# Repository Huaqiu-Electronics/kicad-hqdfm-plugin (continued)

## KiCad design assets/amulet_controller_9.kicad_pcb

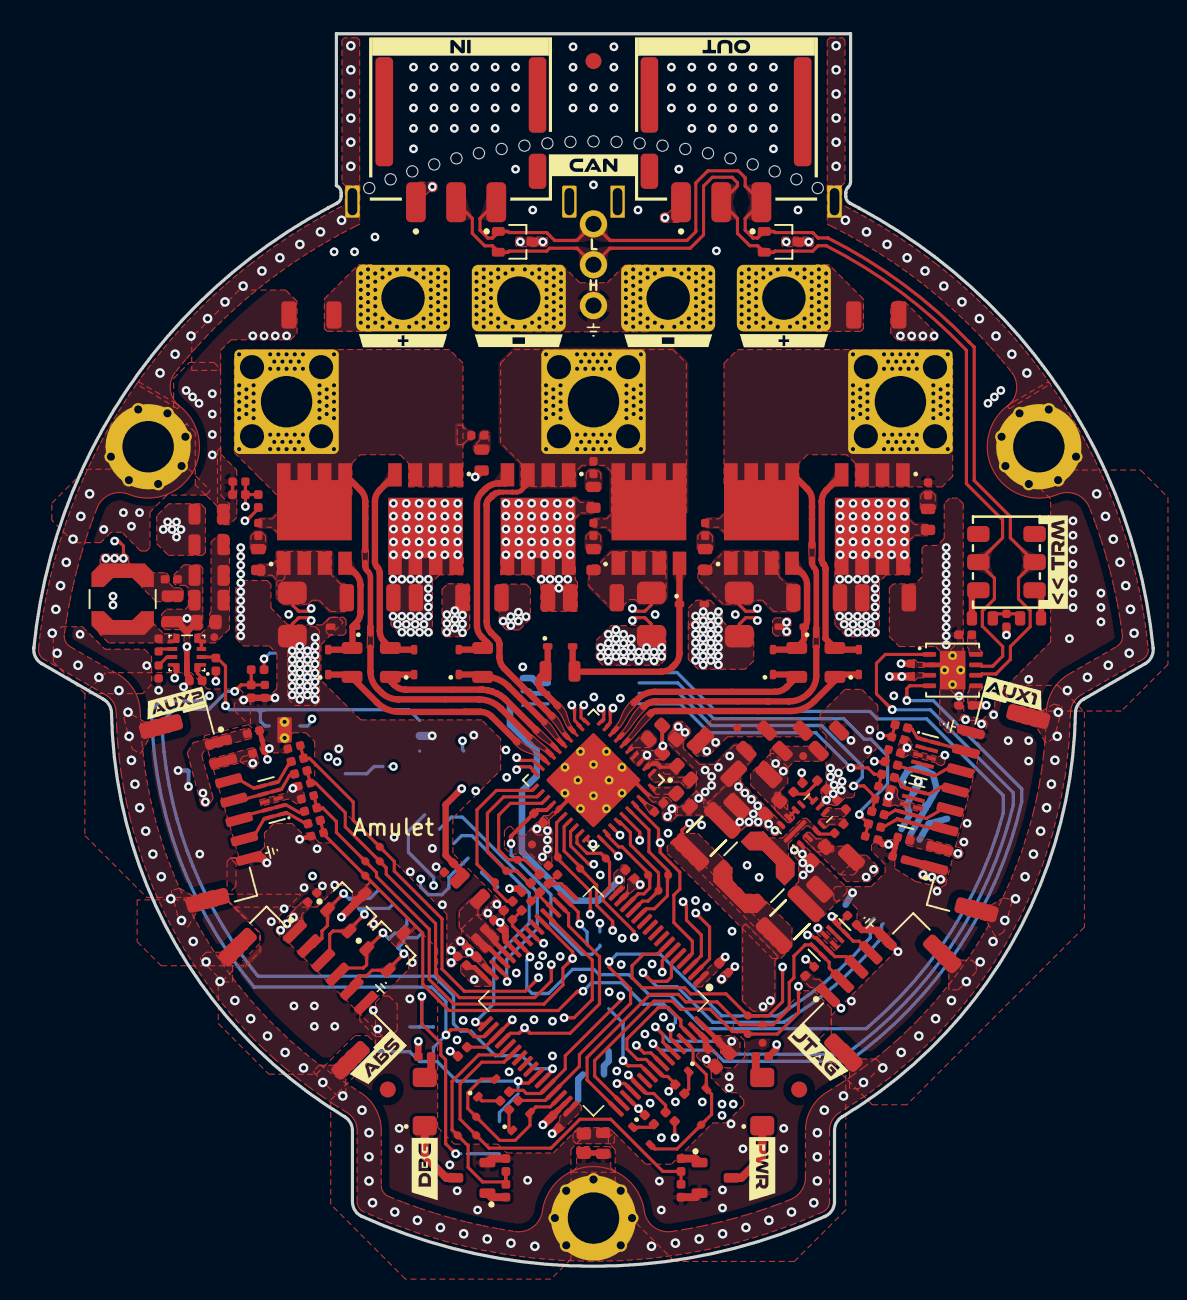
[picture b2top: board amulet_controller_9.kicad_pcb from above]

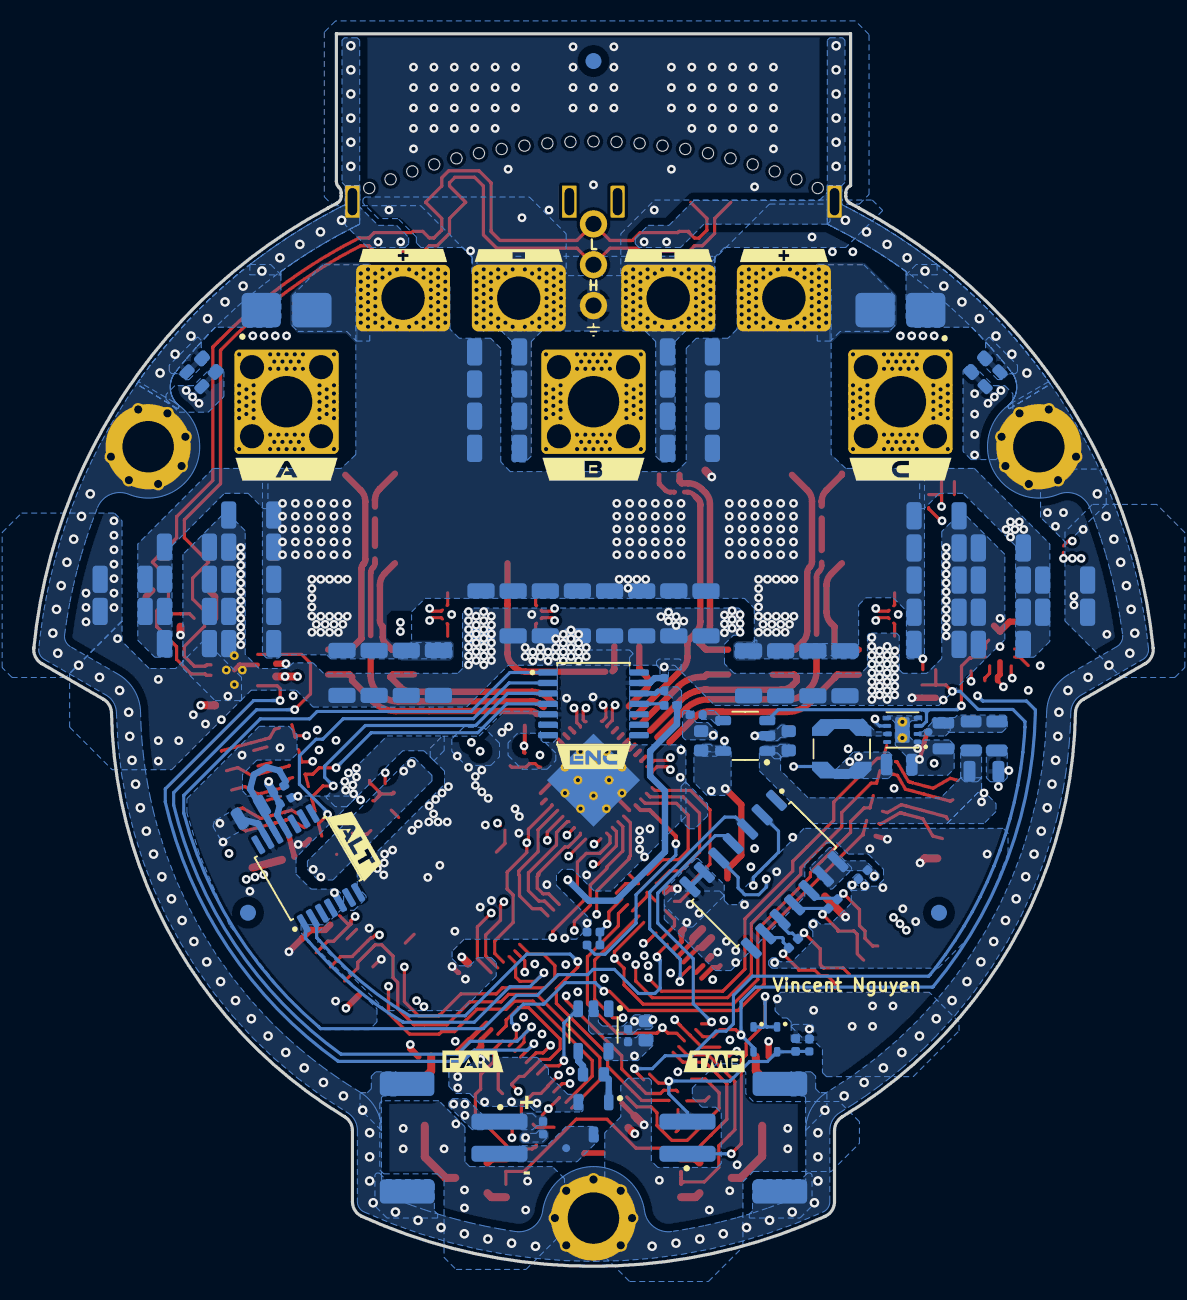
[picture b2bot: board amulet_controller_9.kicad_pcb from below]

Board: 6 copper layers, 69.7 x 76.7 mm, 392 parts (120 on the bottom side), 141 nets.

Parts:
C1, C84, C110: 4u7 X7R 16V; C_0603_1608_DensityHigh
C2, C6, C9, C24, C26: 1u X7R 10V; C_0402_1005_DensityHigh
C3, C4, C5, C8, C10, C11, C27, C28, C29, C101, C102, C103, C104, C105, C107, C108, C109, C111, C112, C113, C114, C115, C125, C126, C127, C128: 100n X7R 50V; C_0402_1005_DensityHigh
C7: 4u7 X5R 25V; C_0402_1005_DensityHigh
C12, C13, C14: 1n X7R 25V; C_0402_1005_DensityHigh
C15, C16, C17, C18, C20, C45, C52: 2u2 X7R 100V; R_0805_2012_DensityHigh
C19, C21, C31, C32, C33, C34, C35, C36, C39, C40, C41, C42, C43, C44, C46, C47, C48, C49, C50, C51, C53, C54, C55, C57, C58, C59, C61, C62, C63, C64, C65, C66, C67, C68, C69, C70, C71, C72, C73, C74, C75, C77, C78, C79, C80, C81, C82, C85, C86, C87: 4u7 X7R 100V; C_1206_3216_DensityHigh
C22, C92: 100n X7R 100V; C_0603_1608_DensityHigh
C23, C25: 220n X7S 100V; C_0603_1608_DensityHigh
C30, C38: 15u X7R 25V; C_1210_3225_DensityHigh
C37, C83: 22u X7R 10V; C_0805_2012_DensityHighest
C56, C106: 10u X7R 25V; C_0805_2012_DensityHighest
C60, C88, C93: 1u X7R 25V; C_0603_1608_DensityHigh
C76: 10n X7R 100V; C_0402_1005_DensityHigh
C89, C96, C98, C100: 4u7 X7R 100V; C_1206_3216_DensityHighest
C90: 100n X7R 16V; C_0402_1005_DensityHigh
C91: 47n X7R 100V; C_0603_1608_DensityHigh
C94: 1u X7R 6.3V; C_0402_1005_DensityHigh
C95, C97, C99: 100n X7R 100V; C_1206_3216_DensityHighest
C116, C117, C118, C119, C120, C121, C122, C123, C124, C133, C134, C135, C136, C137, C138: 3n3 X7R 100V; C_0402_1005_DensityHigh
C129: 4n7 X7R 100V; C_0402_1005_DensityHigh
C130, C131, C132: 1n X7R 1kV; C_0603_1608_DensityHigh
D1, D2: SMBJ51CD-M3/H; DIOM4336X24N
D3, D4, D5, D6, D7, D8, D9, D10, D11, D14, D15, D19, D20, D21, D22: BAT41KFILM; D_SOD-523
D12: YELLOW; LED_SM1206
D13: GREEN; LED_SM1206
D16, D17: PESD4USB5B-TBSX; SOT1176D
D18, D26: PESD4USB3U-TBSX; SOT1176D
D23, D27: CDSOT23-SM712; SOT95P230X110-3N
D24, D25: PESD2CANFD24V-UX; SOT95P230X117-3N
FB1, FB2, FB3, FB4: 1k @ 100MHz; R_0805_2012_DensityHigh
FM1, FM2, FM3, FM4, FM5, FM6: Fiducial; Fiducial_1mm_Mask2mm
H1, H2, H3: M3; MountingHole_3.2mm_M3_Pad_Via
J1: XT60PW-F; AMASS_XT60PW-F_1x02_P7.20mm_Horizontal
J2: XT60PW-M; AMASS_XT60PW-M_1x02_P7.20mm_Horizontal
J3: Phase A; Pad_Square_Vias_6.5x6.5mm
J4: Phase B; Pad_Square_Vias_6.5x6.5mm
J5: Phase C; Pad_Square_Vias_6.5x6.5mm
J6: SM08B-GHS-TB; JST_GH_SM08B-GHS-TB_1x08-1MP_P1.25mm_Horizontal
J7: SM07B-GHS-TB; JST_GH_SM07B-GHS-TB_1x07-1MP_P1.25mm_Horizontal
J8, J9: S2B-PH-SM4-TB; JST_PH_S2B-PH-SM4-TB_1x02-1MP_P2.00mm_Horizontal
J10: SM06B-GHS-TB; JST_GH_SM06B-GHS-TB_1x06-1MP_P1.25mm_Horizontal
J11: PTH 01x03 2.54mm; PTH_1x03_P2.54mm
J12, J13: Nano-Fit 1x03; 1054301203
J14: SM05B-GHS-TB; JST_GH_SM05B-GHS-TB_1x05-1MP_P1.25mm_Horizontal
L1, L2: 22u; L_Coilcraft_LPS4018
L3: 2u2; L_Coilcraft_LPS3314
NT1: FB_5V; NetTie-2_SMD_Pad0.2mm
NT2: FB_12V; NetTie-2_SMD_Pad0.2mm
NT3: VOS_3V3; NetTie-2_SMD_Pad0.2mm
NT4: SRC_HS_A; NetTie-2_SMD_Pad0.4mm
NT5: SHNTA_P; NetTie-2_SMD_Pad0.2mm
NT6: SHNTA_N; NetTie-2_SMD_Pad0.2mm
NT7: SRC_HS_B; NetTie-2_SMD_Pad0.3mm
NT8: SHNTB_P; NetTie-2_SMD_Pad0.2mm
NT9: SHNTB_N; NetTie-2_SMD_Pad0.2mm
NT10: SRC_HS_C; NetTie-2_SMD_Pad0.4mm
NT11: SHNTC_P; NetTie-2_SMD_Pad0.2mm
NT12: SHNTC_N; NetTie-2_SMD_Pad0.2mm
NT13: NTC_MOT_H; NetTie-2_SMD_Pad0.2mm
NT14: NTC_MOT_L; NetTie-2_SMD_Pad0.2mm
Q1, Q2, Q3, Q4, Q5, Q6: TPW1R306PL,L1Q; 2-5S1A
Q7, Q8, Q9: PMV90ENER; SOT-23-3
R1, R2, R3: 22R 1%; R_0402_1005_DensityHigh
R4, R31, R32: 0R; R_0402_1005_DensityHigh
R5, R19, R20, R21, R24, R29: 100k 1%; R_0402_1005_DensityHigh
R6: 9k09 1%; R_0402_1005_DensityHigh
R7, R27, R33: 10k 1%; R_0402_1005_DensityHigh
R8, R9, R28, R44, R45, R46, R47: 2k 1%; R_0402_1005_DensityHigh
R10, R11, R13, R14, R16, R17: 7R5 1% 1/2W; R_0805_2012_DensityHigh
R12, R15, R18: 0m5 1% 2W; HCS1206FTL500
R22, R23, R25, R35, R36, R37, R38, R39, R40, R41, R42, R43, R48, R49: 100R 1% 1/5W; R_0402_1005_DensityHigh
R26: 150R 1% 1/5W; R_0402_1005_DensityHigh
R30: 4k7 1%; R_0402_1005_DensityHigh
R34: 10R 1%; R_0603_1608_DensityHigh
R50, R51: 60R4 1% 1/4W; R_0603_1608_DensityHigh
R52, R53, R54: 0R; R_0603_1608_DensityHigh
R55, R56, R57, R58, R59, R60: 5R 1% 0.4W; R_0603_1608_DensityHigh
SW1: CAS-220TA; CAS-220A_NDC-L
TH1: 47k 1% NTC; R_0402_1005_DensityHigh
TP1: MOTOR_ENABLE; TestPoint_Pad_D0.5mm_Front
TP2: MOTOR_HIZ; TestPoint_Pad_D0.5mm_Front
TP3: MOTOR_FAULT; TestPoint_Pad_D0.5mm_Front
TP4: DRV_SCLK; TestPoint_Pad_D0.5mm_Front
TP5: DRV_MISO; TestPoint_Pad_D0.5mm_Front
TP6: DRV_MOSI; TestPoint_Pad_D0.5mm_Front
TP7: DRV_CS; TestPoint_Pad_D0.5mm_Back
TP8: PWM_PHASEA; TestPoint_Pad_D0.5mm_Front
TP9: PWM_PHASEB; TestPoint_Pad_D0.5mm_Front
TP10: PWM_PHASEC; TestPoint_Pad_D0.5mm_Front
TP11: SOA; TestPoint_Pad_D0.5mm_Front
TP12: SOB; TestPoint_Pad_D0.5mm_Front
TP13: SOC; TestPoint_Pad_D0.5mm_Front
TP14: SWDIO; TestPoint_Pad_D0.5mm_Front
TP15: SWCLK; TestPoint_Pad_D0.5mm_Front
TP16: NRST; TestPoint_Pad_D0.5mm_Front
TP17: AUX1_A; TestPoint_Pad_D0.5mm_Front
TP18: AUX1_B; TestPoint_Pad_D0.5mm_Front
TP19: AUX1_C; TestPoint_Pad_D0.5mm_Front
TP20: AUX1_D; TestPoint_Pad_D0.5mm_Front
TP21: AUX1_E; TestPoint_Pad_D0.5mm_Front
TP22: AUX1_I2C_PULLUP; TestPoint_Pad_D0.5mm_Front
TP23: POS_SENSOR_CS; TestPoint_Pad_D0.5mm_Back
TP24: AUX2_A; TestPoint_Pad_D0.5mm_Front
TP25: AUX2_B; TestPoint_Pad_D0.5mm_Front
TP26: AUX2_C; TestPoint_Pad_D0.5mm_Front
TP27: AUX2_D; TestPoint_Pad_D0.5mm_Front
TP28: AUX2_I2C_PULLUP; TestPoint_Pad_D0.5mm_Front
TP29: RS422_RE; TestPoint_Pad_D0.5mm_Back
TP30: RS422_DE; TestPoint_Pad_D0.5mm_Back
TP31: LED_DBG; TestPoint_Pad_D0.5mm_Front
TP32: LED_PWR; TestPoint_Pad_D0.5mm_Front
TP33: FD_CAN_RX; TestPoint_Pad_D0.5mm_Front
TP34: FDCAN_TX; TestPoint_Pad_D0.5mm_Front
TP35: FAN_CTRL; TestPoint_Pad_D0.5mm_Back
TP36: SENSE_TEMP_MOT; TestPoint_Pad_D0.5mm_Back
TP37: SENSE_TEMP_FET; TestPoint_Pad_D0.5mm_Front
TP38: SENSE_VBAT; TestPoint_Pad_D0.5mm_Front
TP39, TP40, TP41: +VBAT; TestPoint_Pad_D0.5mm_Front
TP42: F_VIN_12V; TestPoint_Pad_D0.5mm_Front
TP43: F_VIN_5V; TestPoint_Pad_D0.5mm_Front
TP44: F_VIN_3V3; TestPoint_Pad_D0.5mm_Back
TP45: +12V; TestPoint_Pad_D0.5mm_Front
TP46: +5V; TestPoint_Pad_D0.5mm_Front
TP47: +5V; TestPoint_Pad_D0.5mm_Back
TP48, TP49: +3V3; TestPoint_Pad_D0.5mm_Front
TP50: +3V3; TestPoint_Pad_D0.5mm_Back
TP51: +A3V3; TestPoint_Pad_D0.5mm_Front
TP52, TP53, TP54, TP55, TP56, TP57: GND; TestPoint_Pad_D0.5mm_Front
TP58: GND; TestPoint_Pad_D0.5mm_Back
TP59: GHA; TestPoint_Pad_D0.4mm_Front
TP60: GLA; TestPoint_Pad_D0.4mm_Front
TP61: SHA; TestPoint_Pad_D0.4mm_Front
TP62: GHB; TestPoint_Pad_D0.4mm_Front
TP63: GLB; TestPoint_Pad_D0.4mm_Front
TP64: SHB; TestPoint_Pad_D0.4mm_Front
TP65: GHC; TestPoint_Pad_D0.4mm_Front
TP66: GLC; TestPoint_Pad_D0.4mm_Front
TP67: SHC; TestPoint_Pad_D0.4mm_Front
TP68: SA_P; TestPoint_Pad_D0.5mm_Front
TP69: SA_N; TestPoint_Pad_D0.5mm_Front
TP70: SB_P; TestPoint_Pad_D0.5mm_Front
TP71: SB_N; TestPoint_Pad_D0.5mm_Front
TP72: SC_P; TestPoint_Pad_D0.5mm_Front
TP73: SC_N; TestPoint_Pad_D0.5mm_Front
TP74: FAN_SW; TestPoint_Pad_D0.5mm_Back
U1: STM32G474RET3; LQFP-64_10x10mm_P0.5mm
U2: LMR36506MSC5RPERQ1; LMR36503
U3: LMR36006FSCQ; LMR36006
U4: TPS62172DSG; WSON-8-1EP_2x2mm_P0.5mm_EP0.9x1.6mm_ThermalVias
U5: LP2992IM5-3.3/NOPB; SOT95P280X145-5N
U6: DRV8353FS; WQFN-40-1EP_6x6mm_P0.5mm_EP4.15x4.15mm_ThermalVias
U7: AS5047P; SOP-14_4.4x5mm_P0.65mm_H1.2mm
U8: AS5048B; SOP-14_4.4x5mm_P0.65mm_H1.2mm
U9: SN65HVD35DR; SOIC-14 5.4mm
U10: TCAN1051HGVDRBRQ1; HVSON-8-1EP_3x3mm_P0.65mm_EP1.6x2.4mm_ThermalVias
U11: DGD0216WT-7; SOT-23-5
kibuzzard-657CE6B7: G***; kibuzzard-657CE6B7
kibuzzard-657CE6F4: G***; kibuzzard-657CE6F4
kibuzzard-657CE8E9: G***; kibuzzard-657CE8E9
kibuzzard-657CE8F0: G***; kibuzzard-657CE8F0
kibuzzard-657CE701: G***; kibuzzard-657CE701
kibuzzard-657CE738: G***; kibuzzard-657CE738
kibuzzard-657DB620: G***; kibuzzard-657DB620
kibuzzard-657EBC7A: G***; kibuzzard-657EBC7A
kibuzzard-657EBC30: G***; kibuzzard-657EBC30
kibuzzard-657EBCD6: G***; kibuzzard-657EBCD6
kibuzzard-657EBD3F: G***; kibuzzard-657EBD3F
kibuzzard-657EBDD6: G***; kibuzzard-657EBDD6
kibuzzard-657EBE81: G***; kibuzzard-657EBE81
kibuzzard-657EBEA6: G***; kibuzzard-657EBEA6
kibuzzard-657F78ED, kibuzzard-657F78ED#2, kibuzzard-657F78ED#3, kibuzzard-657F78ED#4: G***; kibuzzard-657F78ED
kibuzzard-657F7953, kibuzzard-657F7953#2, kibuzzard-657F7953#3, kibuzzard-657F7953#4: G***; kibuzzard-657F7953
kibuzzard-65803F12: G***; kibuzzard-65803F12
kibuzzard-658032A4: G***; kibuzzard-658032A4
kibuzzard-6580330B: G***; kibuzzard-6580330B
kibuzzard-65807142: G***; kibuzzard-65807142
kibuzzard-65807156: G***; kibuzzard-65807156

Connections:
+3V3: C1.1, C3.1, C4.1, C5.1, C8.1, C9.1, C83.1, C104.1, C105.1, C107.1, C108.1, C114.1, C115.1, C127.1, J6.2, J7.2, J14.1, L3.2, NT3.2, R8.1, R9.1, R31.1, R32.1, TP48.1, TP49.1, TP50.1, U1.1 (VBAT), U1.16 (VDD), U1.32 (VDD), U1.48 (VDD), U1.64 (VDD), U7.12 (VDD3V3), U8.11 (VDD5V), U9.13 (VCC), U9.14 (VCC), U10.5 (VIO)
+5V: C29.1, C37.1, C45.1, C60.1, C109.1, C110.1, C111.1, C112.1, C113.1, C126.1, FB4.1, J6.1, J7.1, J10.1, L1.2, NT1.1, R7.2, R23.2, R26.1, TP46.1, TP47.1, U5.1 (VIN), U10.3 (VCC), U11.5 (VCC)
+12V: C30.1, C38.1, C125.1, J9.1, L2.2, NT2.2, TP45.1
+A3V3: C2.1, C84.1, C90.1, D14.1 (K), D15.1 (K), FB1.1, NT13.1, R19.1, TH1.1, TP51.1, U5.5 (VOUT), U6.24 (VREF)
+VBAT: C15.1, C16.1, C31.1, C32.1, C33.1, C34.1, C35.1, C36.1, C39.1, C40.1, C41.1, C42.1, C43.1, C44.1, C46.1, C47.1, C48.1, C49.1, C50.1, C51.1, C53.1, C54.1, C55.1, C57.1, C58.1, C59.1, C61.1, C62.1, C63.1, C64.1, C65.1, C66.1, C67.1, C68.1, C69.1, C70.1, C71.1, C72.1, C73.1, C74.1, C75.1, C77.1, C78.1, C79.1, C80.1, C81.1, C82.1, C85.1, C86.1, C87.1, C88.1, C89.1, C92.1, C95.1, C96.1, C97.1, C98.1, C99.1, C100.1, D1.2 (A2), D2.2 (A2), FB2.1, FB3.1, J1.2, J2.2, Q1.5 (D), Q1.6 (D), Q1.7 (D), Q1.8 (D), Q3.5 (D), Q3.6 (D), Q3.7 (D), Q3.8 (D), Q5.5 (D), Q5.6 (D), Q5.7 (D), Q5.8 (D), R29.1, R58.2, R59.2, R60.2, TP39.1, TP40.1, TP41.1, U6.3 (VM), U6.4 (VDRAIN)
/Project Architecture/Interface - FD-CAN/FDCAN_N: D24.1 (K1), D25.1 (K1), J11.3, J12.3, J13.3, SW1.2 (B), U10.6 (CANL)
/Project Architecture/Interface - FD-CAN/FDCAN_P: D24.2 (K2), D25.2 (K2), J11.2, J12.2, J13.2, SW1.5 (B), U10.7 (CANH)
/Project Architecture/Interface - FD-CAN/FDCAN_RX: TP33.1, U1.58 (PB5), U10.4 (RXD)
/Project Architecture/Interface - FD-CAN/FDCAN_S: R33.1, U10.8 (S)
/Project Architecture/Interface - FD-CAN/FDCAN_TX: TP34.1, U1.59 (PB6), U10.1 (TXD)
/Project Architecture/Interface - Fan Control/FAN_GATE: Q9.1 (G), R34.2
/Project Architecture/Interface - Fan Control/FAN_OUT: R34.1, U11.4 (OUT)
/Project Architecture/Interface - Fan Control/FAN_SW: J9.2, Q9.3 (D), TP74.1
/Project Architecture/Interface - Interconnects/AUX1P_A: D18.5 (K), D18.6 (K), J6.3, R35.1
/Project Architecture/Interface - Interconnects/AUX1P_B: D18.4 (K), D18.7 (K), J6.4, R36.1
/Project Architecture/Interface - Interconnects/AUX1P_C: D18.1 (K), D18.10 (K), J6.5, R37.1
/Project Architecture/Interface - Interconnects/AUX1P_D: D16.5 (K), D16.6 (K), J6.6, R38.1
/Project Architecture/Interface - Interconnects/AUX1P_E: D16.1 (K), D16.10 (K), J6.7, R39.1
/Project Architecture/Interface - Interconnects/AUX1_A: C124.1, R35.2, TP17.1, U1.19 (PA5), U1.36 (PB14), U7.2 (CLK)
/Project Architecture/Interface - Interconnects/AUX1_B: C122.1, R36.2, TP18.1, U1.57 (PB4), U7.3 (MISO)
/Project Architecture/Interface - Interconnects/AUX1_C: C120.1, R37.2, TP19.1, U1.21 (PA7), U7.4 (MOSI)
/Project Architecture/Interface - Interconnects/AUX1_D: C118.1, R38.2, R44.2, TP20.1, U1.51 (PA15), U9.2 (R)
/Project Architecture/Interface - Interconnects/AUX1_D_K: D19.1 (K), R44.1
/Project Architecture/Interface - Interconnects/AUX1_E: C116.1, R39.2, R46.2, TP21.1, U1.56 (PB3), U1.62 (PB9), U9.5 (D)
/Project Architecture/Interface - Interconnects/AUX1_E_K: D21.1 (K), R46.1
/Project Architecture/Interface - Interconnects/AUX1_I2C_PULLUP: D19.2 (A), D21.2 (A), TP22.1, U1.61 (PB8)
/Project Architecture/Interface - Interconnects/AUX2P_A: D17.5 (K), D17.6 (K), J7.3, R40.1
/Project Architecture/Interface - Interconnects/AUX2P_B: D17.4 (K), D17.7 (K), J7.4, R41.1
/Project Architecture/Interface - Interconnects/AUX2P_C: D17.2 (K), D17.9 (K), J7.5, R42.1
/Project Architecture/Interface - Interconnects/AUX2P_D: D17.1 (K), D17.10 (K), J7.6, R43.1
/Project Architecture/Interface - Interconnects/AUX2_A: C123.1, R40.2, TP24.1, U1.6 (PF1)
/Project Architecture/Interface - Interconnects/AUX2_B: C121.1, R41.2, R45.2, TP25.1, U1.5 (PF0), U1.44 (PA10), U8.1 (SDA)
/Project Architecture/Interface - Interconnects/AUX2_B_K: D20.1 (K), R45.1
/Project Architecture/Interface - Interconnects/AUX2_C: C119.1, R42.2, R47.2, TP26.1, U1.22 (PC4), U1.45 (PA11), U8.2 (SCL)
/Project Architecture/Interface - Interconnects/AUX2_C_K: D22.1 (K), R47.1
/Project Architecture/Interface - Interconnects/AUX2_D: C117.1, R43.2, TP27.1, U1.60 (PB7)
/Project Architecture/Interface - Interconnects/AUX2_I2C_PULLUP: D20.2 (A), D22.2 (A), TP28.1, U1.46 (PA12)
/Project Architecture/Interface - Interconnects/CAN_TERM_B: R51.2, SW1.4 (A)
/Project Architecture/Interface - Interconnects/CAN_TERM_MID: C129.1, R50.2, R51.1
/Project Architecture/Interface - Interconnects/CAN_TERM_T: R50.1, SW1.1 (A)
/Project Architecture/Interface - Interconnects/NRST: C128.1, D26.1 (K), D26.10 (K), J14.4, TP16.1, U1.7 (PG10)
/Project Architecture/Interface - Interconnects/NTC_MOT_H: J8.1, NT13.2
/Project Architecture/Interface - Interconnects/NTC_MOT_L: J8.2, NT14.2
/Project Architecture/Interface - Interconnects/POS_SENSOR_CS: TP23.1, U1.26 (PB2), U7.1 (~CS)
/Project Architecture/Interface - Interconnects/RS422_D+: D23.2 (A2), J10.5, R49.2, U9.9 (Y)
/Project Architecture/Interface - Interconnects/RS422_D-: D23.1 (A1), J10.4, R49.1, U9.10 (Z)
/Project Architecture/Interface - Interconnects/RS422_R+: D27.1 (A1), J10.2, R48.1, U9.12 (A)
/Project Architecture/Interface - Interconnects/RS422_R-: D27.2 (A2), J10.3, R48.2, U9.11 (B)
/Project Architecture/Interface - Interconnects/SWCLK: D26.4 (K), D26.7 (K), J14.3, TP15.1, U1.50 (PA14)
/Project Architecture/Interface - Interconnects/SWDIO: D26.5 (K), D26.6 (K), J14.2, TP14.1, U1.49 (PA13)
/Project Architecture/Interface - RS-422/RS422_DE: TP30.1, U1.33 (PB11), U9.4 (DE)
/Project Architecture/Interface - RS-422/RS422_~RE: TP29.1, U1.30 (PB10), U9.3 (~RE)
/Project Architecture/MCU - IOs/BOARD_VERSION: R19.2, R20.1, U1.18 (PA4)
/Project Architecture/MCU - IOs/DRV_CS: TP7.1, U1.24 (PB0), U6.30 (nSCS)
/Project Architecture/MCU - IOs/DRV_MISO: R9.2, TP5.1, U1.53 (PC11), U6.27 (SDO)
/Project Architecture/MCU - IOs/DRV_MOSI: TP6.1, U1.2 (PC13), U6.28 (SDI)
/Project Architecture/MCU - IOs/DRV_SCLK: TP4.1, U1.52 (PC10), U6.29 (SCLK)
/Project Architecture/MCU - IOs/FAN_CTRL: TP35.1, U1.55 (PD2), U11.3 (IN)
/Project Architecture/MCU - IOs/FILTER_SOA: C12.1, R1.1, U1.17 (PA3)
/Project Architecture/MCU - IOs/FILTER_SOB: C13.1, R2.1, U1.20 (PA6)
/Project Architecture/MCU - IOs/FILTER_SOC: C14.1, R3.1, U1.25 (PB1)
/Project Architecture/MCU - IOs/LED_DBG: R21.1, R22.1, TP31.1, U1.37 (PB15)
/Project Architecture/MCU - IOs/LED_PWR: R24.1, R25.1, TP32.1, U1.38 (PC6)
/Project Architecture/MCU - IOs/MOTOR_ENABLE: TP1.1, U1.3 (PC14), U6.31 (ENABLE)
/Project Architecture/MCU - IOs/MOTOR_FAULT: R8.2, TP3.1, U1.35 (PB13), U6.26 (nFAULT)
/Project Architecture/MCU - IOs/MOTOR_HIZ: TP2.1, U1.4 (PC15), U6.33 (INLA), U6.35 (INLB), U6.37 (INLC)
/Project Architecture/MCU - IOs/PWM_PHASEA: TP8.1, U1.14 (PA2), U6.32 (INHA)
/Project Architecture/MCU - IOs/PWM_PHASEB: TP9.1, U1.13 (PA1), U6.34 (INHB)
/Project Architecture/MCU - IOs/PWM_PHASEC: TP10.1, U1.12 (PA0), U6.36 (INHC)
/Project Architecture/MCU - IOs/SENSE_TEMP_FET: C101.1, D14.2 (A), R27.1, TH1.2, TP37.1, U1.34 (PB12)
/Project Architecture/MCU - IOs/SENSE_TEMP_MOT: C102.1, D15.2 (A), NT14.1, R28.1, TP36.1, U1.42 (PA8)
/Project Architecture/MCU - IOs/SENSE_VBAT: C103.1, R29.2, R30.1, TP38.1, U1.43 (PA9)
/Project Architecture/MCU - IOs/SOA: R1.2, TP11.1, U6.23 (SOA)
/Project Architecture/MCU - IOs/SOB: R2.2, TP12.1, U6.22 (SOB)
/Project Architecture/MCU - IOs/SOC: R3.2, TP13.1, U6.21 (SOC)
/Project Architecture/MCU - Power/F_A3V3: C6.1, C7.1, C10.1, C11.1, FB1.2, U1.28 (VREF+), U1.29 (VDDA)
/Project Architecture/Motor Control - Top Level/CPH: C91.1, U6.2 (CPH)
/Project Architecture/Motor Control - Top Level/CPL: C91.2, U6.1 (CPL)
/Project Architecture/Motor Control - Top Level/DVDD: C94.1, U6.38 (DVDD)
/Project Architecture/Motor Control - Top Level/GHA: D4.1 (K), R10.2, TP59.1, U6.6 (GHA)
/Project Architecture/Motor Control - Top Level/GHB: D7.1 (K), R13.1, TP62.1, U6.15 (GHB)
/Project Architecture/Motor Control - Top Level/GHC: D10.1 (K), R16.1, TP65.1, U6.16 (GHC)
/Project Architecture/Motor Control - Top Level/GLA: D5.1 (K), R11.1, TP60.1, U6.8 (GLA)
/Project Architecture/Motor Control - Top Level/GLB: D8.1 (K), R14.1, TP63.1, U6.13 (GLB)
/Project Architecture/Motor Control - Top Level/GLC: D11.1 (K), R17.1, TP66.1, U6.18 (GLC)
/Project Architecture/Motor Control - Top Level/Motor Control - Inverter/FET_GHA: D4.2 (A), Q1.4 (G), R10.1
/Project Architecture/Motor Control - Top Level/Motor Control - Inverter/FET_GHB: D7.2 (A), Q3.4 (G), R13.2
/Project Architecture/Motor Control - Top Level/Motor Control - Inverter/FET_GHC: D10.2 (A), Q5.4 (G), R16.2
/Project Architecture/Motor Control - Top Level/Motor Control - Inverter/FET_GLA: D3.1 (K), D5.2 (A), Q2.4 (G), R11.2
/Project Architecture/Motor Control - Top Level/Motor Control - Inverter/FET_GLB: D6.1 (K), D8.2 (A), Q4.4 (G), R14.2
/Project Architecture/Motor Control - Top Level/Motor Control - Inverter/FET_GLC: D9.1 (K), D11.2 (A), Q6.4 (G), R17.2
/Project Architecture/Motor Control - Top Level/Motor Control - Inverter/PHA: C133.2, C136.1, J3.1, NT4.2, Q1.1 (S), Q1.2 (S), Q1.3 (S), Q2.5 (D), Q2.6 (D), Q2.7 (D), Q2.8 (D)
/Project Architecture/Motor Control - Top Level/Motor Control - Inverter/PHB: C134.2, C137.1, J4.1, NT7.2, Q3.1 (S), Q3.2 (S), Q3.3 (S), Q4.5 (D), Q4.6 (D), Q4.7 (D), Q4.8 (D)
/Project Architecture/Motor Control - Top Level/Motor Control - Inverter/PHC: C135.2, C138.1, J5.1, NT10.2, Q5.1 (S), Q5.2 (S), Q5.3 (S), Q6.5 (D), Q6.6 (D), Q6.7 (D), Q6.8 (D)
/Project Architecture/Motor Control - Top Level/Motor Control - Inverter/SNUBH_A: C136.2, R58.1
/Project Architecture/Motor Control - Top Level/Motor Control - Inverter/SNUBH_B: C137.2, R59.1
/Project Architecture/Motor Control - Top Level/Motor Control - Inverter/SNUBH_C: C138.2, R60.1
/Project Architecture/Motor Control - Top Level/Motor Control - Inverter/SNUBL_A: C133.1, R55.2
/Project Architecture/Motor Control - Top Level/Motor Control - Inverter/SNUBL_B: C134.1, R56.2
/Project Architecture/Motor Control - Top Level/Motor Control - Inverter/SNUBL_C: C135.1, R57.2
/Project Architecture/Motor Control - Top Level/Motor Control - Inverter/SRC_LS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: C95.2, NT5.1, Q2.1 (S), Q2.2 (S), Q2.3 (S), R12.2, R55.1
/Project Architecture/Motor Control - Top Level/Motor Control - Inverter/SRC_LS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: C97.2, NT8.2, Q4.1 (S), Q4.2 (S), Q4.3 (S), R15.2, R56.1
/Project Architecture/Motor Control - Top Level/Motor Control - Inverter/SRC_LS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: C99.2, NT11.2, Q6.1 (S), Q6.2 (S), Q6.3 (S), R18.2, R57.1
/Project Architecture/Motor Control - Top Level/SA_N: NT6.1, TP69.1, U6.10 (SNA)
/Project Architecture/Motor Control - Top Level/SA_P: NT5.2, TP68.1, U6.9 (SPA)
/Project Architecture/Motor Control - Top Level/SB_N: NT9.1, TP71.1, U6.11 (SNB)
/Project Architecture/Motor Control - Top Level/SB_P: NT8.1, TP70.1, U6.12 (SPB)
/Project Architecture/Motor Control - Top Level/SC_N: NT12.1, TP73.1, U6.20 (SNC)
/Project Architecture/Motor Control - Top Level/SC_P: NT11.1, TP72.1, U6.19 (SPC)
/Project Architecture/Motor Control - Top Level/SHA: NT4.1, TP61.1, U6.7 (SHA)
/Project Architecture/Motor Control - Top Level/SHB: NT7.1, TP64.1, U6.14 (SHB)
/Project Architecture/Motor Control - Top Level/SHC: NT10.1, TP67.1, U6.17 (SHC)
/Project Architecture/Motor Control - Top Level/VCP: C88.2, U6.5 (VCP)
/Project Architecture/Motor Control - Top Level/VGLS: C93.1, U6.40 (VGLS)
/Project Architecture/Power - Generation/ADJ_A3V3: C76.1, U5.4 (ADJ)
/Project Architecture/Power - Generation/BOOT_5V: C27.2, U2.6 (BOOT)
/Project Architecture/Power - Generation/BOOT_12V: C28.2, U3.4 (BOOT)
/Project Architecture/Power - Generation/FB_5V: NT1.2, U2.8 (FB)
/Project Architecture/Power - Generation/FB_12V: NT2.1, R5.1
/Project Architecture/Power - Generation/FB_DIV_12V: R5.2, R6.1, U3.7 (FB)
/Project Architecture/Power - Generation/F_VIN_3V3: C52.1, C56.1, FB4.2, TP44.1, U4.2 (VIN)
/Project Architecture/Power - Generation/F_VIN_5V: C17.1, C20.1, C22.1, FB2.2, TP43.1, U2.3 (EN/UVLO), U2.4 (VIN)
/Project Architecture/Power - Generation/F_VIN_12V: C18.1, C19.1, C21.1, C23.1, C25.1, FB3.2, TP42.1, U3.2 (VIN), U3.9 (EN), U3.10 (VIN)
/Project Architecture/Power - Generation/MODE_5V: R4.1, U2.1 (MODE/SYNC)
/Project Architecture/Power - Generation/PG_5V: R7.1, U2.2 (PGOOD), U4.3 (EN), U5.3 (ON/~OFF)
/Project Architecture/Power - Generation/SW_3V3: L3.1, U4.7 (SW)
/Project Architecture/Power - Generation/SW_5V: C27.1, L1.1, U2.5 (SW)
/Project Architecture/Power - Generation/SW_12V: C28.1, L2.1, U3.3 (NC), U3.12 (SW)
/Project Architecture/Power - Generation/VCC_5V: C24.1, U2.7 (VCC)
/Project Architecture/Power - Generation/VCC_12V: C26.1, U3.5 (VCC)
/Project Architecture/Power - Generation/VOS_3V3: NT3.1, U4.6 (VOS)
/Project Architecture/Sensing - Position/COMM_VDD: R31.2, U7.11 (VDD)
/Project Architecture/Sensing - Position/DIS_VDD3V: C106.1, R32.2, U8.12 (VDD3V)
/Project Architecture/User - LED Indicators/DBG_G: Q7.1 (G), R22.2
/Project Architecture/User - LED Indicators/LED_DBG_A: D12.2 (A), R23.1
/Project Architecture/User - LED Indicators/LED_DBG_K: D12.1 (K), Q7.3 (D)
/Project Architecture/User - LED Indicators/LED_PWR_A: D13.2 (A), R26.2
/Project Architecture/User - LED Indicators/LED_PWR_K: D13.1 (K), Q8.3 (D)
/Project Architecture/User - LED Indicators/PWR_G: Q8.1 (G), R25.2
CHASSIS: C130.1, C131.1, C132.1, D1.1 (A1), D2.1 (A1), D24.3 (CC), D25.3 (CC), H1.1, H2.1, H3.1, J1.MP2, J2.MP2, J6.MP1, J6.MP2, J7.MP1, J7.MP2, J8.MP1, J8.MP2, J9.MP1, J9.MP2, J10.MP1, J10.MP2, J14.MP1, J14.MP2, R52.1, R53.1, R54.1
GND: C1.2, C2.2, C3.2, C4.2, C5.2, C6.2, C7.2, C8.2, C9.2, C10.2, C11.2, C12.2, C13.2, C14.2, C15.2, C16.2, C17.2, C18.2, C19.2, C20.2, C21.2, C22.2, C23.2, C24.2, C25.2, C26.2, C29.2, C30.2, C31.2, C32.2, C33.2, C34.2, C35.2, C36.2, C37.2, C38.2, C39.2, C40.2, C41.2, C42.2, C43.2, C44.2, C45.2, C46.2, C47.2, C48.2, C49.2, C50.2, C51.2, C52.2, C53.2, C54.2, C55.2, C56.2, C57.2, C58.2, C59.2, C60.2, C61.2, C62.2, C63.2, C64.2, C65.2, C66.2, C67.2, C68.2, C69.2, C70.2, C71.2, C72.2, C73.2, C74.2, C75.2, C76.2, C77.2, C78.2, C79.2, C80.2, C81.2, C82.2, C83.2, C84.2, C85.2, C86.2, C87.2, C89.2, C90.2, C92.2, C93.2, C94.2, C96.2, C98.2, C100.2, C101.2, C102.2, C103.2, C104.2, C105.2, C106.2, C107.2, C108.2, C109.2, C110.2, C111.2, C112.2, C113.2, C114.2, C115.2, C116.2, C117.2, C118.2, C119.2, C120.2, C121.2, C122.2, C123.2, C124.2, C125.2, C126.2, C127.2, C128.2, C129.2, C130.2, C131.2, C132.2, D3.2 (A), D6.2 (A), D9.2 (A), D16.3 (A), D16.8 (A), D17.3 (A), D17.8 (A), D18.3 (A), D18.8 (A), D23.3 (common), D26.3 (A), D26.8 (A), D27.3 (common), J1.1, J2.1, J6.8, J7.7, J10.6, J11.1, J12.1, J13.1, J14.5, NT6.2, NT9.2, NT12.2, Q7.2 (S), Q8.2 (S), Q9.2 (S), R4.2, R6.2, R12.1, R15.1, R18.1, R20.2, R21.2, R24.2, R27.2, R28.2, R30.2, R33.2, R52.2, R53.2, R54.2, TP52.1, TP53.1, TP54.1, TP55.1, TP56.1, TP57.1, TP58.1, U1.15 (VSS), U1.27 (VSSA), U1.31 (VSS), U1.47 (VSS), U1.63 (VSS), U2.9 (GND), U3.1 (PGND), U3.6 (AGND), U3.11 (PGND), U4.1 (PGND), U4.4 (AGND), U4.5 (FB), U4.9 (PAD), U5.2 (GND), U6.25 (AGND), U6.39 (GND), U6.41 (EP), U7.5 (TST), U7.13 (GND), U8.5 (TEST), U8.13 (GND), U9.6 (GND), U9.7 (GND), U10.2 (GND), U10.9 (PAD), U11.2 (COM)

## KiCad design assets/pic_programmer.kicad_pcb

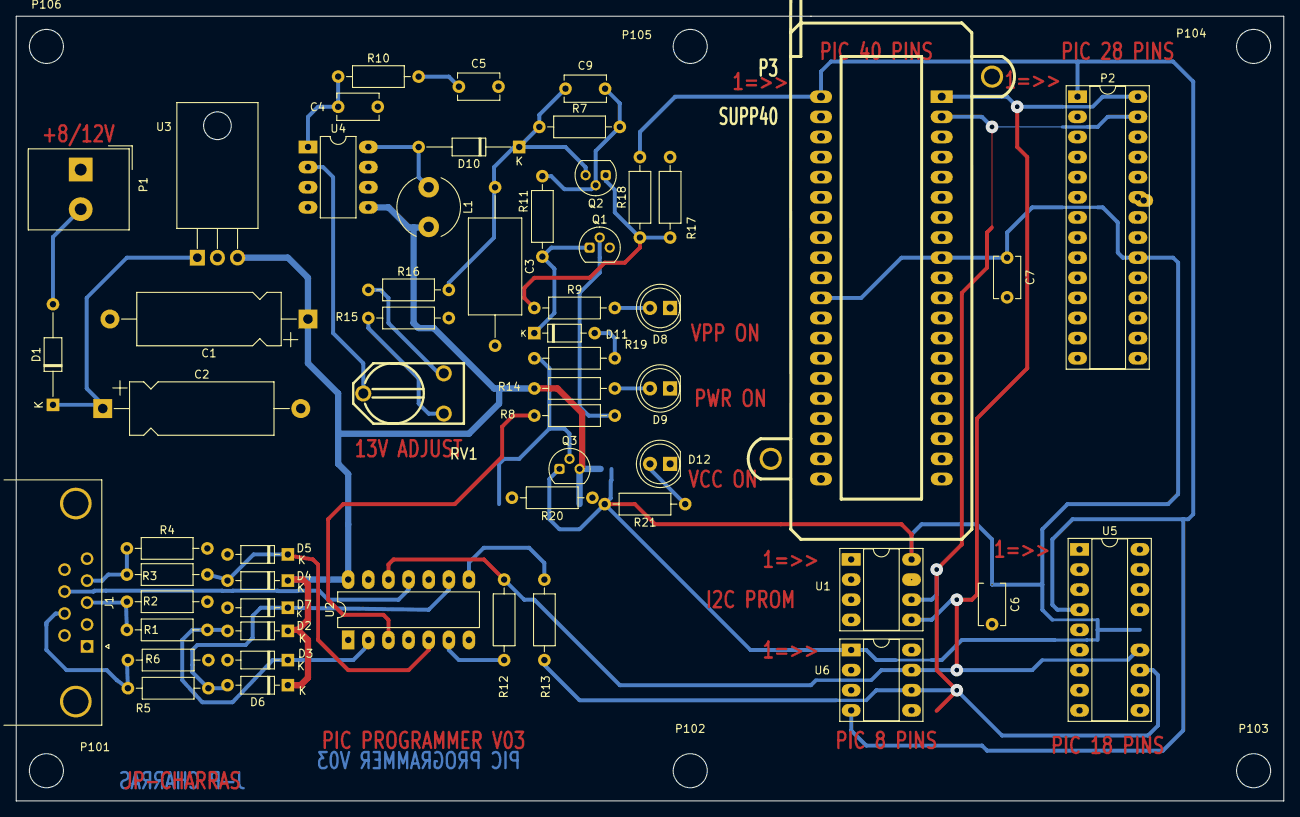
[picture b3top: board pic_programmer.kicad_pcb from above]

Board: 2 copper layers, 160.0 x 99.1 mm, 63 parts (1 on the bottom side), 34 nets.

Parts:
C1: 100µF; CP_Axial_L18.0mm_D6.5mm_P25.00mm_Horizontal
C2: 220uF; CP_Axial_L18.0mm_D6.5mm_P25.00mm_Horizontal
C3: 22uF/25V; C_Axial_L12.0mm_D6.5mm_P20.00mm_Horizontal
C4: 0; C_Disc_D5.1mm_W3.2mm_P5.00mm
C5: 10nF; C_Disc_D5.1mm_W3.2mm_P5.00mm
C6, C7: 100nF; C_Disc_D5.1mm_W3.2mm_P5.00mm
C9: 220nF; C_Disc_D5.1mm_W3.2mm_P5.00mm
D1: 1N4004; D_DO-35_SOD27_P12.70mm_Horizontal
D2, D3, D4, D5, D6, D7, D11: BAT43; D_DO-35_SOD27_P7.62mm_Horizontal
D8: RED-LED; LED_D5.0mm
D9: GREEN-LED; LED_D5.0mm
D10: SCHOTTKY; D_DO-35_SOD27_P12.70mm_Horizontal
D12: YELLOW-LED; LED_D5.0mm
J1: DB9-FEMAL; DSUB-9_Female_Horizontal_P2.77x2.84mm_EdgePinOffset7.70mm_H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
JP1: JUMPER; SolderJumper-2_P1.3mm_Open_TrianglePad1.0x1.5mm
L1: 22uH; L_Radial_D7.8mm_P5.00mm_Fastron_07HCP
P1: CONN_2; Altech_AK300_1x02_P5.00mm_45-Degree
P2: SUPP28; DIP-28_W7.62mm_Socket_LongPads
P3: SUPP40; 40tex-Ell600
P101, P102, P103, P104, P105, P106: CONN_1; MountingHole_4.3mm_M4
Q1: BC237; TO-92
Q2, Q3: BC307; TO-92
R1, R2, R3, R4, R5, R6, R7: 10K; R_Axial_DIN0207_L6.3mm_D2.5mm_P10.16mm_Horizontal
R8: 1K; R_Axial_DIN0207_L6.3mm_D2.5mm_P10.16mm_Horizontal
R9, R19, R20: 2.2K; R_Axial_DIN0207_L6.3mm_D2.5mm_P10.16mm_Horizontal
R10: 5,1K; R_Axial_DIN0207_L6.3mm_D2.5mm_P10.16mm_Horizontal
R11, R17: 22K; R_Axial_DIN0207_L6.3mm_D2.5mm_P10.16mm_Horizontal
R12, R13, R14, R21: 470; R_Axial_DIN0207_L6.3mm_D2.5mm_P10.16mm_Horizontal
R15: 6.2K; R_Axial_DIN0207_L6.3mm_D2.5mm_P10.16mm_Horizontal
R16: 62K; R_Axial_DIN0207_L6.3mm_D2.5mm_P10.16mm_Horizontal
R18: 220; R_Axial_DIN0207_L6.3mm_D2.5mm_P10.16mm_Horizontal
RV1: 1K; RV2X4
U1: 24Cxx; DIP-8_W7.62mm_Socket_LongPads
U2: 74HC125; DIP-14_W7.62mm_LongPads
U3: 7805; TO-220-3_Horizontal_TabDown
U4: LT1373; DIP-8_W7.62mm_LongPads
U5: PIC_18_PINS; DIP-18_W7.62mm_Socket_LongPads
U6: PIC_8_PINS; DIP-8_W7.62mm_Socket_LongPads

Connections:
/CLOCK-RB6: P2.27, P3.39, R13.2, U1.6 (SCL), U5.12 (ICSPC/RB6), U6.6 (GP1)
/DATA-RB7: P2.28, P3.40, R12.2, U1.5 (SDA), U2.12, U5.13 (ICSPD/RB7), U6.7 (GP0)
/PC-CLOCK-OUT: J1.7, R5.1, R6.1
/PC-DATA-IN: J1.8, U2.11
/PC-DATA-OUT: J1.4, R3.1, R4.1
/VPP_ON: J1.3, R1.1, R2.1
/VPP/MCLR: P2.1, P3.1, R18.2, U5.4 (MCLR), U6.4 (GP3/MCLR)
/pic_sockets/VCC_PIC: C6.1, C7.1, JP1.2, P2.20, P3.11, P3.32, Q3.1 (C), R21.2, U1.8 (VCC), U5.14 (VDD), U6.1 (VDD)
GND: C1.2, C2.2, C3.2, C4.2, C5.2, C6.2, C7.2, D3.2 (A), D5.2 (A), D7.2 (A), D8.1 (K), D9.1 (K), D12.1 (K), J1.5, P1.1, P2.8, P2.19, P3.8, P3.12, P3.31, Q1.3 (E), R2.2, R4.2, R6.2, R15.2, R17.2, U1.1 (A0), U1.2 (A1), U1.3 (A2), U1.4 (GND), U2.1, U2.4, U2.7 (GND), U2.10, U2.13, U3.2 (GND), U4.6 (GND_S), U4.7 (GND), U5.5 (VSS), U6.8 (VSS)
unnamed: C5.1, R10.2
unnamed: D1.2 (A), P1.2 (PM)
unnamed: C2.1, D1.1 (K), U3.1 (VI)
unnamed: D2.2 (A), D3.1 (K), R1.2, U2.2
unnamed: D4.2 (A), D5.1 (K), P2.23, R3.2, U2.5
unnamed: D6.2 (A), D7.1 (K), R5.2, U2.9
unnamed: D8.2 (A), R9.2
unnamed: D9.2 (A), R14.2
unnamed: D10.2 (A), L1.1, U4.8 (Vsw)
unnamed: D11.2 (A), R19.1
unnamed: D11.1 (K), Q1.1 (C), R11.1
unnamed: D12.2 (A), R21.1
unnamed: Q1.2 (B), R8.2
unnamed: C9.2, Q2.2 (B), R7.2, R11.2
unnamed: Q2.1 (C), R9.1, R17.1, R18.1
unnamed: Q3.2 (B), R19.2, R20.2
unnamed: R8.1, U2.3
unnamed: R12.1, U2.6
unnamed: R13.1, U2.8
unnamed: R15.1, RV1.1
unnamed: R16.1, RV1.3
unnamed: RV1.2, U4.2 (FB+)
unnamed: C4.1, R10.1, U4.1 (Vc)
VCC: C1.1, D2.1 (K), D4.1 (K), D6.1 (K), JP1.1, L1.2, Q3.3 (E), R14.1, R20.1, U2.14 (VCC), U3.3 (VO), U4.5 (Vin)
VPP: C3.1, C9.1, D10.1 (K), Q2.3 (E), R7.1, R16.2

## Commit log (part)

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2024-02-21 add README_CN.md
2024-02-21 add to kicad-huaqiu
2024-02-22 fix image path function
2024-02-29 simplify code
2024-02-29 mac test
2024-02-29 initial version code
2024-03-08 fix child_frame
2024-03-08 commit usable version 0.3.0
2024-03-08 fix inch unit problem
2024-03-19 perfect dfm code
2024-03-22 first step modify
2024-04-02 modify icon to hqdfm
2024-05-17 modify display color
2024-05-31 modify show color
2024-06-03 modify request analysis
2024-06-06 modify child frame
2024-06-07 modify translate
2024-06-14 modify dfm drawing method
2024-06-14 modify graphics setting
2024-06-17 complete introduction
2024-06-19 modify board item getting method
2024-06-19 modify box selected
2024-06-21 modify hqdfm name
2024-06-21 modify readme
2024-06-26 modify to requset json file
2024-06-26 modify readmeq
2024-07-05 complete board edge method
2024-07-24 Add link between readme and readme_cn
2024-08-26 complete plugin
2024-10-22 modify PermissionError
2024-11-20 add kicad-qh install
2024-11-28 add license
2024-11-28 modify license
2024-12-10 Make path parsing stray-space resilient
2026-03-24 feat: update multiple modules and add new features
2026-03-26 modify GitItem to ResolveItem
2026-04-30 Upgrade repo infrastructure: uv, ruff, pre-commit, CI, pytest, Pydantic models, type annotations, mkdocs
    - uv-based dev environment with Makefile targets (install, lint, format,
    typecheck, test, pure-test, docs-build, pre-commit)
    - ruff check with 15 rule sets — 0 errors, 0 redundant ignores
    - pre-commit hooks (ruff check+format, typos, pre-commit-hooks v6)
    - pcbnew stub module for running tests outside KiCad
    - 150 pytest tests covering pure functions, Pydantic models, colour
2026-04-30 Add headless CLI mode for local DFM analysis
    - kicad_dfm/headless.py: pcbnew-only analysis runner (no wx, no cloud)
    - AnalysisReport and CheckResult dataclasses
    - analyze_board() loads board and runs local checks
    - Exit codes: 0=pass, 1=warn, 2=fail
    - kicad_dfm/cli.py: argparse CLI with check subcommand
    - --output flag for JSON report file
